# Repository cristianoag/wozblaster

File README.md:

# The Wozblaster (Reloaded)

## Introduction 
The WozBlaster OPL4 cartridge is a sound expansion device designed for the MSX platform. This cartridge enables a range of additional audio capabilities for the MSX, including support for both FM synthesis and wavetable synthesis. 

At its core is the OPL4 (FM Operator Type-L4) sound chip, which was developed by Yamaha and used in a variety of electronic musical instruments and computer sound cards. 

With the WozBlaster OPL4 cartridge, MSX computer users can enjoy high-quality sound and create complex musical arrangements with ease.

.jpg)

The WozBlaster cartridge is an external sound device designed for the MSX platform. It is a clone of the Moonsound and allows access to the advanced capabilities of the OPL4 sound chip for MSX games and other OPL4-compatible music software. The cartridge was originally designed by Gustavo Iriarte.

The OPL4 sound chip from Yamaha is typically paired with a YAC513 floating-point DAC chip, or an alternative compatible DAC chip. The YMF278 is an enhanced version of the OPL3 and, although not officially part of the standard, has been widely adopted by the MSX community, particularly in Europe.

Moonsound clones generally come equipped with 1 MB of sample-RAM and a 2 MB Yamaha YRW801-M General MIDI ROM. Although the board has the capacity to address more than 1 MB of memory, the original version of the Wozblaster only had two 512K memory chips.

It's worth noting that the original Wozblaster PCB cannot be fitted into a traditional MSX cartridge case. Additionally, as detailed in the building instructions, the audio jack holes on the original board are quite small, which made it difficult to find a connector that would fit.

## Original Wozblaster

Image below shows the original Wozblaster cartridge PCB:

|PCB Side 1|PCB Side 2|
|---|---|
|.jpg)|.jpg)|

A few reloaded versions of the WozBlaster cartridge have been created with appropriately-sized holes to fit both Konami and Patola cartridge cases. Additionally, the audio jack holes have been enlarged to accommodate most common audio jack connectors. Some versions of the cartridge are still a work in progress.

## Reloaded Versions

Currently, the following versions of the WozBlaster cartridge are available (please note that this list is subject to change as new versions become available):

* [Wozblaster Reloaded v1.1](/hardware/reloaded_v1.1) - Based on the original circuit, this version features a combination of through-hole and surface-mount components. The board is smaller and can fit in both Konami and Patola cases. (tested and working)

|PCB Side 1|PCB Side 2|
|---|---|
|.jpg)|.jpg)|

* [Wozblaster Reloaded v1.3](/hardware/reloaded_v1.3) - This version replaces the old 27C160 EPROM with an AM29F016B flash memory, and all passive components are 0603 SMD. The sound is injected back to SOUNDIN in mono. The board is smaller and can fit in both Konami and Patola cases. (abandoned)
  
* [Wozblaster Reloaded v3.3](/hardware/reloaded_v3.3/) - Version based on the UDA1334 DAC, and using the [Adafruit A1334 DAC Module](https://github.com/adafruit/Adafruit-UDA1334A-I2S-Stereo-DAC-PCB) to perform the digital to analog conversion. It is injecting audio back into the SOUNDIN MSX pin. It features 1MB of RAM and 2MB of ROM with MIDI compatible samples. (tested and working)

|PCB Side 1|PCB Side 2|
|---|---|
|||

* [Wozblaster Reloaded v4.0](/hardware/reloaded_v4.0/) - Evolution of v3.3 featuring a 2MB CY62167ELL RAM integrated. It also mixes the computer SOUNDIN. (tested and working)

|PCB Side 1|PCB Side 2|
|---|---|
|.jpg)|.jpg)|

* [Wozblaster Reloaded v4.5](/hardware/reloaded_v4.5/) - This version is now using the EPM7064STC44 (or EPM7032STC400) CPLD to replace the GAL16V8D it also better isolates the audio channels  before injecting them as mono back to the MSX SOUNDIN. (tested and working)

|PCB Side 1|PCB Side 2|
|---|---|
|.jpg)|.jpg)|

## Bill of Materials

The Bill of Materials (BOM) for each version of the WozBlaster cartridge is available in the respective page. The BOM includes a list of all the components needed to build the cartridge, as well as links to purchase the components online.

## Box and Inlay Trays

The Wozblaster Reloaded has a box designed by Adriano Souza to fit the cartridge. The box is available in the [box](/box) folder.

Although a paper inlay is provided to secure the cartridge inside the box, it is  recommended to use a plastic insert inner tray (bed) for additional protection, especially during transportation. These trays can be purchased from AliExpress at the following link: [AliExpress Tray](https://s.click.aliexpress.com/e/_DDVBv2D).

## Resources

This GitHub repository contains all of the resources needed to build both the original WozBlaster cartridge and the reloaded versions. For detailed instructions, you can refer to the article I wrote, which includes an updated bill of materials (BOM) with links to purchase the required components. You can find the article at https://theretrohacker.com/2022/12/31/blasting-sound-for-your-msx-the-wozblaster-reloaded/.

The update on the v3.1 development has been posted on a short YouTube video in english [here](https://youtu.be/J95RrFSF2NM). 

The update on v3.2 is available on a quick video [here](https://www.youtube.com/shorts/V5VmL33uvzE). 

Each folder contains detailed Bill of Materials for each version of the board, as well as the Gerber files needed to manufacture the PCBs. 

## License 

This work is licensed under a [Creative Commons Attribution-NonCommercial-ShareAlike 4.0 International License](http://creativecommons.org/licenses/by-nc-sa/4.0/).

* If you remix, transform, or build upon the material, you must distribute your contributions under the same license as the original.
* You may not use the material for commercial purposes.
* You must give appropriate credit, provide a link to the license, and indicate if changes were made. You may do so in any reasonable manner, but not in any way that suggests the licensor endorses you or your use.

**ATTENTION**

This project was made for the retro community and not for commercial purposes. So only retro hardware forums and individual people can build this project.

THE SALE OF ANY PART OF THIS PROJECT WITHOUT EXPRESS AUTHORIZATION IS PROHIBITED!

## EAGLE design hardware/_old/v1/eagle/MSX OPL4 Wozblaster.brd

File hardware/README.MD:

# The Wozblaster (Reloaded)

## Content of this folder:

* [27C160 Adapter](/hardware/27c160-tl866-adapter) - This folder contains the files necessary to build an adapter that allows you to program the 27C160 EPROM on inexpensive TL866 programmers.
* [GAL16V8 JEDEC](/hardware/gal16v8d) - This folder contains the fuse file required to program the GAL16V8 SPLD with the selection circuit needed for the Wozblasters.
* [YRW801-M ROM] - This folder contains the binary content needed to program flash or EPROMs with the contents of the YRW801-M (MIDI Samples).
* [Wozblaster v1](hardware/v1) - This folder contains the original Wozblaster board created by Gustavo Iriarte. (Released)
* [Wozblaster Reloaded v1.1](/hardware/reloaded_v1.1) - Based on the original circuit, this version features a combination of through-hole and surface-mount components. The board is smaller and can fit in both Konami and Patola cases. (Released)
* [Wozblaster Reloaded v1.2](/hardware/reloaded_v1.2) - This version replaces the old 27C160 EPROM with an AM29F016B flash, and all passive components are 0603 SMD. The sound is injected back to SOUNDIN in mono. The board is smaller and can fit in both Konami and Patola cases. (In development)
* [Wozblaster Reloaded v2.0](/hardware/reloaded_v2) - This version features an AM29F016B flash in place of the 27C160 EPROM, all passive components are 0603 SMD, and the YAC513 DAC is replaced by a NEC UPD6376. The sound is injected back to SOUNDIN in mono, and the LF347 OP Amps are replaced with 4558s. The audio circuit has been improved, and the board is smaller and can fit in both Konami and Patola cases. (In development)

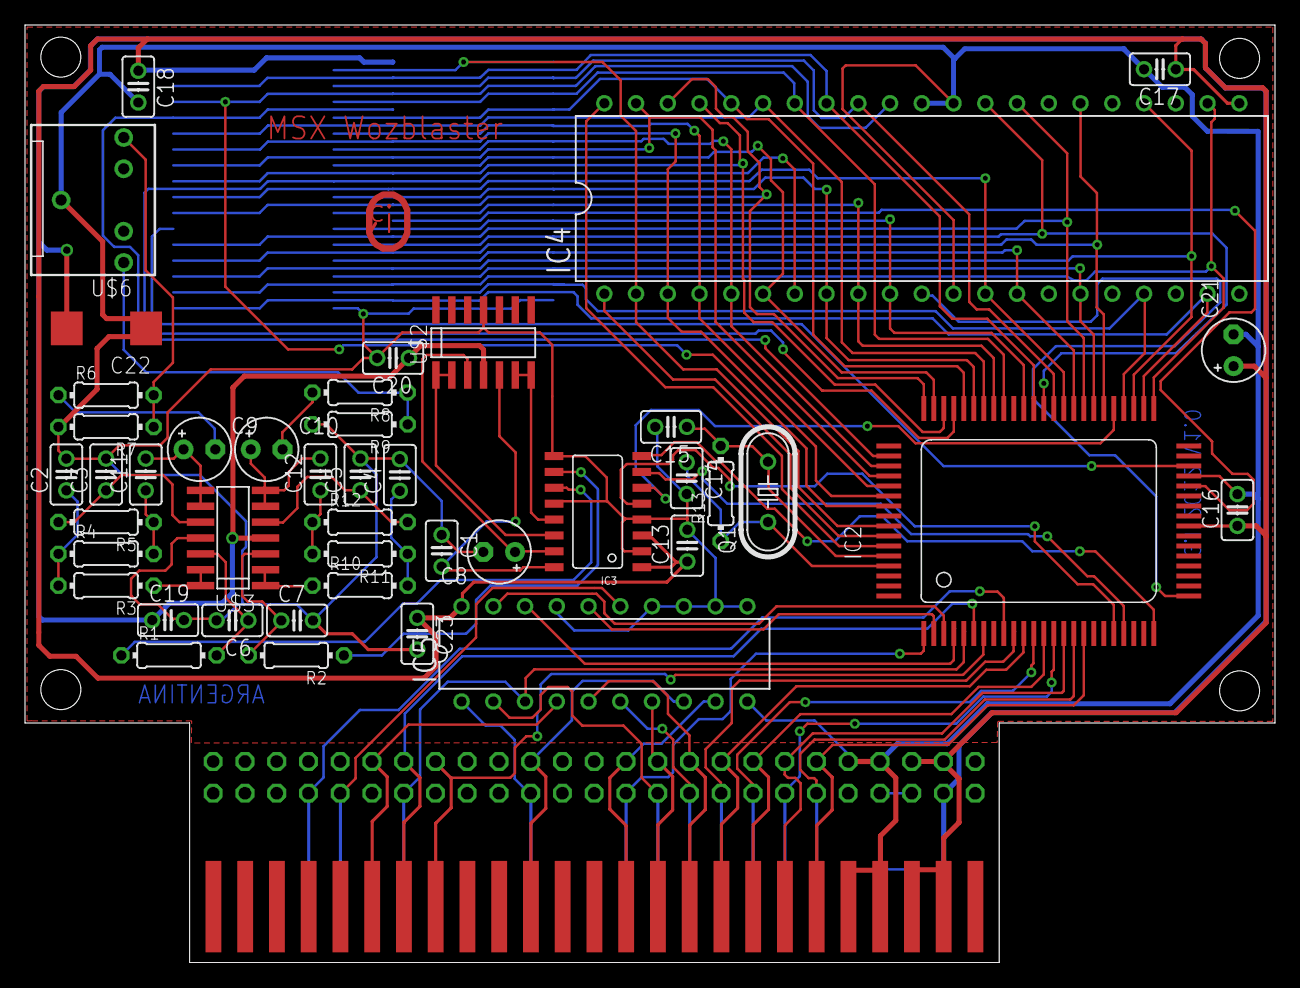
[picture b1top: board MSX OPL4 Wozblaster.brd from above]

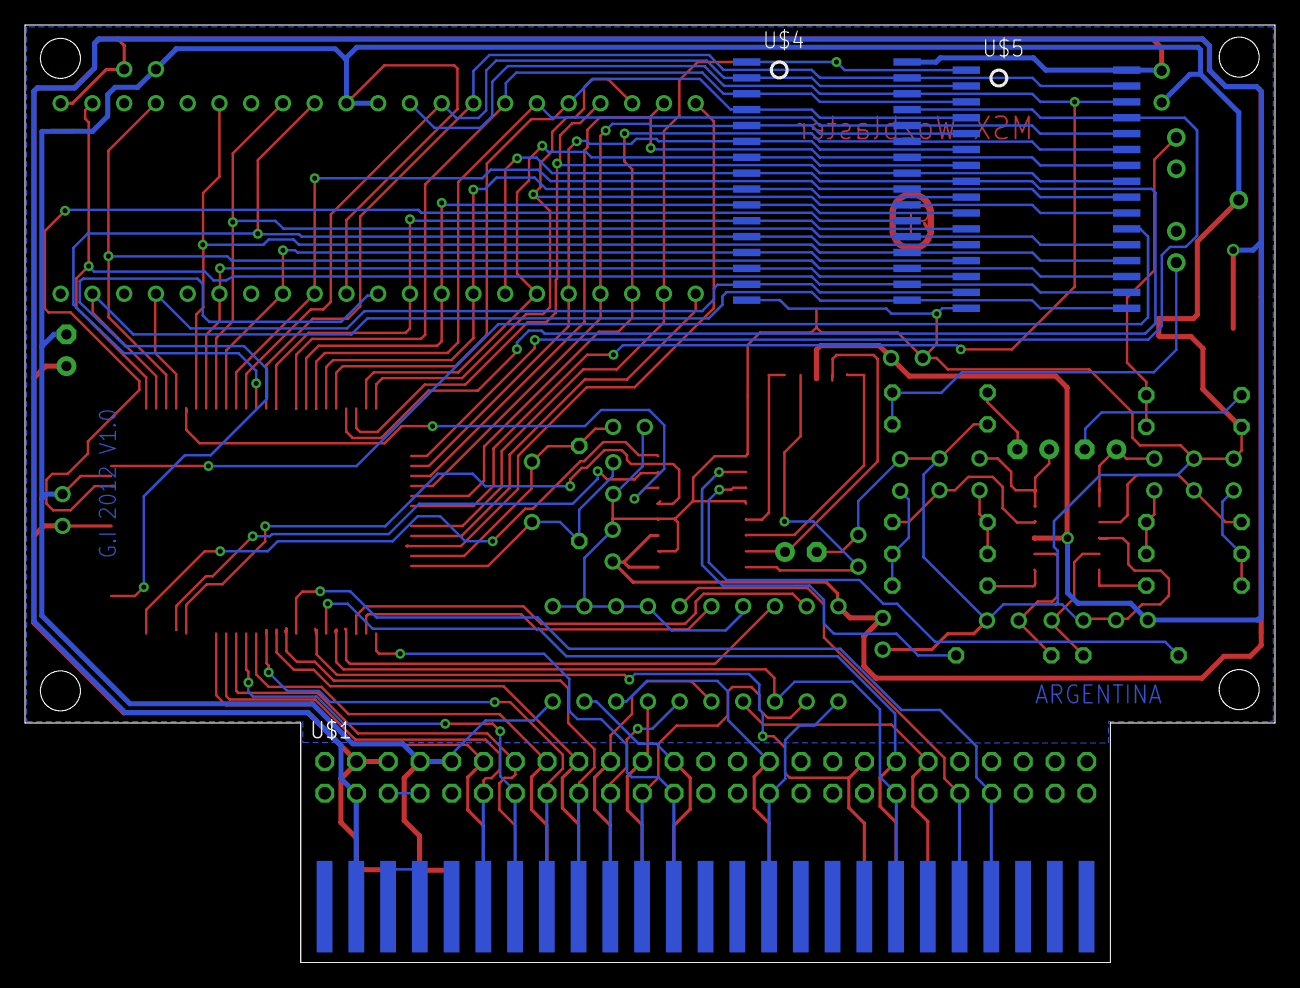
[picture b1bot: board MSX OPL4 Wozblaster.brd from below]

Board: 2 copper layers, 100.0 x 75.0 mm, 48 parts (4 on the bottom side), 93 nets.

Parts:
C1, C4, C5, C12, C13, C14, C15, C16, C17, C18, C23: C2.5-2
C2: 0.015uf; C2.5-2
C3, C6, C7: 2200p; C2.5-2
C8, C9, C10, C21: E2,5-5
C11: 0.039uf; C2.5-2
C19, C20: 100nf; C2.5-2
C22: D/7343-31R
IC1: OPL4_10X10; OPL410X10
IC2: YMF278B-F; 80-QFP
IC3: YAC513-M; 16SOP
IC4: DIL42
IC5: ATF16V8BP3; DIL20
Q1: 33.8688; HC49/S
R1, R2: 360k; 0204/7
R3, R4, R5, R8, R10, R11, R12: 1k; 0204/7
R6: 1; 0204/7
R7, R9: 100k; 0204/7
R13: 3.3k; 0204/7
U$1: 50PINCONN; MSX50PINHEADER
U$2, U$3: LF347SO14; SO14-2
U$4, U$5: SRAM4MBIT; SOP32L
U$6: MSXJACK; 1501_06

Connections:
+12V: C19.1, C20.1, C22.+, IC1.+12V, U$1.P48, U$2.4, U$3.4
A0: IC2.52.MA0, IC4.30, U$4.12, U$5.12
A1: IC2.54.MA1, IC4.10, U$4.11, U$5.11
A2: IC2.57.MA2, IC4.9, U$4.10, U$5.10
A3: IC2.59.MA3, IC4.8, U$4.9, U$5.9
A4: IC2.61.MA4, IC4.7, U$4.8, U$5.8
A5: IC2.63.MA5, IC4.6, U$4.7, U$5.7
A6: IC2.67.MA6, IC4.5, U$4.6, U$5.6
A7: IC2.69.MA7, IC4.4, U$4.5, U$5.5
A8: IC2.70.MA8, IC4.3, U$4.27, U$5.27
A9: IC2.68.MA9, IC4.41, U$4.26, U$5.26
A10: IC2.64.MA10, IC4.40, U$4.23, U$5.23
A11: IC2.62.MA11, IC4.39, U$4.25, U$5.25
A12: IC2.60.MA12, IC4.38, U$4.4, U$5.4
A13: IC2.58.MA13, IC4.37, U$4.28, U$5.28
A14: IC2.56.MA14, IC4.36, U$4.3, U$5.3
A15: IC2.53.MA15, IC4.35, U$4.31, U$5.31
A16: IC2.51./MA16, IC4.34, U$4.2, U$5.2
A17: IC2.71.MA17, IC4.33, U$4.30, U$5.30
A18: IC2.73.MA18, IC4.2, U$4.1, U$5.1
A19: IC2.74.MA19, IC4.1
A20: IC2.75.MA20, IC4.42
AA0: IC1.A0, IC2.1.A0, U$1.P28
AA1: IC1.A1, IC5.9, U$1.P27
AA2: IC1.A2, IC5.2, U$1.P30
AA3: IC1.A3, IC5.7, U$1.P29
AA4: IC1.A4, IC5.6, U$1.P32
AA5: IC1.A5, IC5.5, U$1.P31
AA6: IC1.A6, IC5.1, U$1.P22
AA7: IC1.A7, IC5.8, U$1.P21
GND: C1.1, C2.2, C3.2, C4.2, C5.2, C6.2, C7.2, C8.-, C13.2, C14.2, C15.2, C16.2, C17.2, C18.2, C19.2, C20.2, C21.-, C22.-, C23.2, IC1.GND1, IC1.GND2, IC2.37.VSS, IC3.2, IC3.4, IC3.9, IC3.12, IC4.12, IC4.31, IC4.32, IC5.10, IC5.11, IC5.12, IC5.13, IC5.14, IC5.17, R7.2, R9.2, U$1.P41, U$1.P43, U$2.11, U$3.11, U$4.16, U$5.16, U$6.1
MD0: IC2.49.MD0, IC4.14, U$4.13, U$5.13
MD1: IC2.47.MD1, IC4.16, U$4.14, U$5.14
MD2: IC2.44.WD2, IC4.18, U$4.15, U$5.15
MD3: IC2.42.WD3, IC4.20, U$4.17, U$5.17
MD4: IC2.41.WD4, IC4.23, U$4.18, U$5.18
MD5: IC2.43.WD5, IC4.25, U$4.19, U$5.19
MD6: IC2.46.MD6, IC4.27, U$4.20, U$5.20
MD7: IC2.48.MD7, IC4.29, U$4.21, U$5.21
unnamed: IC1.D0, IC2.10./D0, U$1.P34
unnamed: IC1.D1, IC2.11.D1, U$1.P33
unnamed: IC1.D2, IC2.12.D2, U$1.P36
unnamed: IC1.D3, IC2.13.D3, U$1.P35
unnamed: IC1.D4, IC2.14.D4, U$1.P38
unnamed: IC1.D5, IC2.15.D5, U$1.P37
unnamed: IC1.D6, IC2.16.D6, U$1.P40
unnamed: IC1.D7, IC2.17.D7, U$1.P39
unnamed: IC1./RD, IC2.5./RD, IC5.3, U$1.P14
unnamed: IC1./IORQ, IC5.4, U$1.P11
unnamed: IC2.3.A2, IC5.19
unnamed: IC2.4./CS, IC5.18
unnamed: IC2.2.A1, IC5.16
unnamed: IC1./BUSDIR, IC5.15, U$1.P10
unnamed: C1.2, IC3.16, U$2.5
unnamed: IC3.14, U$2.1, U$2.2
unnamed: IC3.11, R1.1
unnamed: C6.1, R1.2, U$3.12
unnamed: R3.1, U$3.13, U$3.14
unnamed: C2.1, R3.2, R4.1
unnamed: C11.1, R4.2, R5.1
unnamed: C3.1, R5.2, U$3.10
unnamed: C9.+, C11.2, U$3.8, U$3.9
unnamed: C10.-, R8.2
unnamed: R6.2, R7.1, U$6.2
unnamed: C7.1, R2.2, U$3.3
unnamed: R10.1, U$3.1, U$3.2
unnamed: C4.1, R10.2, R11.1
unnamed: C12.1, R11.2, R12.1
unnamed: C5.1, R12.2, U$3.5
unnamed: C10.+, C12.2, U$3.6, U$3.7
unnamed: C9.-, R6.1
unnamed: R8.1, R9.1, U$6.5
unnamed: IC3.10, R2.1
unnamed: C8.+, IC3.15, U$2.3
unnamed: IC3.13, U$2.6, U$2.7
unnamed: IC2.20.BCO, IC3.5
unnamed: IC2.45.WCO, IC3.6
unnamed: IC2.21.LRO, IC3.7
unnamed: IC2.24.DO2, IC3.8
unnamed: C15.1, IC2.76.XO, Q1.2, R13.2
unnamed: C14.1, IC2.77.XI, Q1.1, R13.1
unnamed: IC2.25./MCS0, IC4.11
unnamed: IC2.50./MRD, IC4.13, U$4.24, U$5.24
unnamed: IC2.36./MCS6, U$4.22
unnamed: IC2.38./MCS7, U$5.22
unnamed: IC2.66./MWR, U$4.29, U$5.29
unnamed: IC1.SW1, IC1.SW2
unnamed: U$1.P44, U$1.P46
unnamed: IC1./WR, IC2.6./WR, U$1.P13
unnamed: IC1./INT, IC2.9./IRQ, U$1.P8
unnamed: IC1./RESET, IC2.7./IC, U$1.P15
unnamed: C23.1, IC5.20
VCC: C13.1, C16.1, C17.1, C18.1, C21.+, IC1.+5V1, IC1.+5V2, IC2.32.VDD, IC3.1, IC3.3, IC4.22, U$1.P45, U$1.P47, U$4.32, U$5.32

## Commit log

2023-01-01 initial load
2023-01-01 images and labels
2023-01-01 hardware folder
2023-01-01 adapter to program the eprom
2023-01-01 software
2023-01-02 fixes to the PCB
2023-01-02 save project kicad
2023-01-02 soundin version
2023-01-02 removing backups
2023-01-02 case for the wozblaster v1
2023-01-02 fixes
2023-01-03 iteractions of the case
2023-01-04 Additional Images and labels
2023-01-09 fixing images
2023-01-10 JED fix
2023-01-20 conversion fixes
2023-02-20 v1.2 and v2 work in progress
2023-02-20 Readme Updates
2023-02-20 Hardware Readme
2023-02-20 Readme adjustments
2023-02-20 Text Improvements
2023-02-20 PCB image
2023-02-20 Uploading Gerbers vor v1.2
2023-03-22 v3 and multiple adjusts
2023-04-21 Reloaded 3.1
2023-04-21 minor changes to README
2023-04-21 footprints for 3.1
2023-04-21 Update video on the description
2023-05-16 v3.2
2023-06-06 v3.3 update
2023-06-06 footprint adjustments
2023-08-27 v4.0 upload and README adjustments
2023-09-24 Footprint adjustments, README, small fixes
2023-09-26 gerbers
2024-03-10 License
2024-03-10 README update
2024-03-10 README
2024-03-14 Update images
2024-10-13 v5.0 initial upload
2024-11-16 new verilog selection code. readme adjustments for v5
2024-11-17 verilog code for v5
2024-11-17 datasheets and readme update
2024-11-18 cpld code and pcb adjustments after tests
2024-11-19 7032 cpld files
2024-11-19 ibom update
2024-11-19 readme.md update
2026-02-14 New version 4.6. New CPLD code to solve issues with TurboR
